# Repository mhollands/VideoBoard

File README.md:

# VideoBoard
Repo to hold files for the video board which was a prototype for the HP2VGA project

# Known Issues
Vsync and Hsync are swapped. C23 and C32 are unnecessary. Solution, use C23 and C32 footprints to swap the Vsync and Hsync inputs.

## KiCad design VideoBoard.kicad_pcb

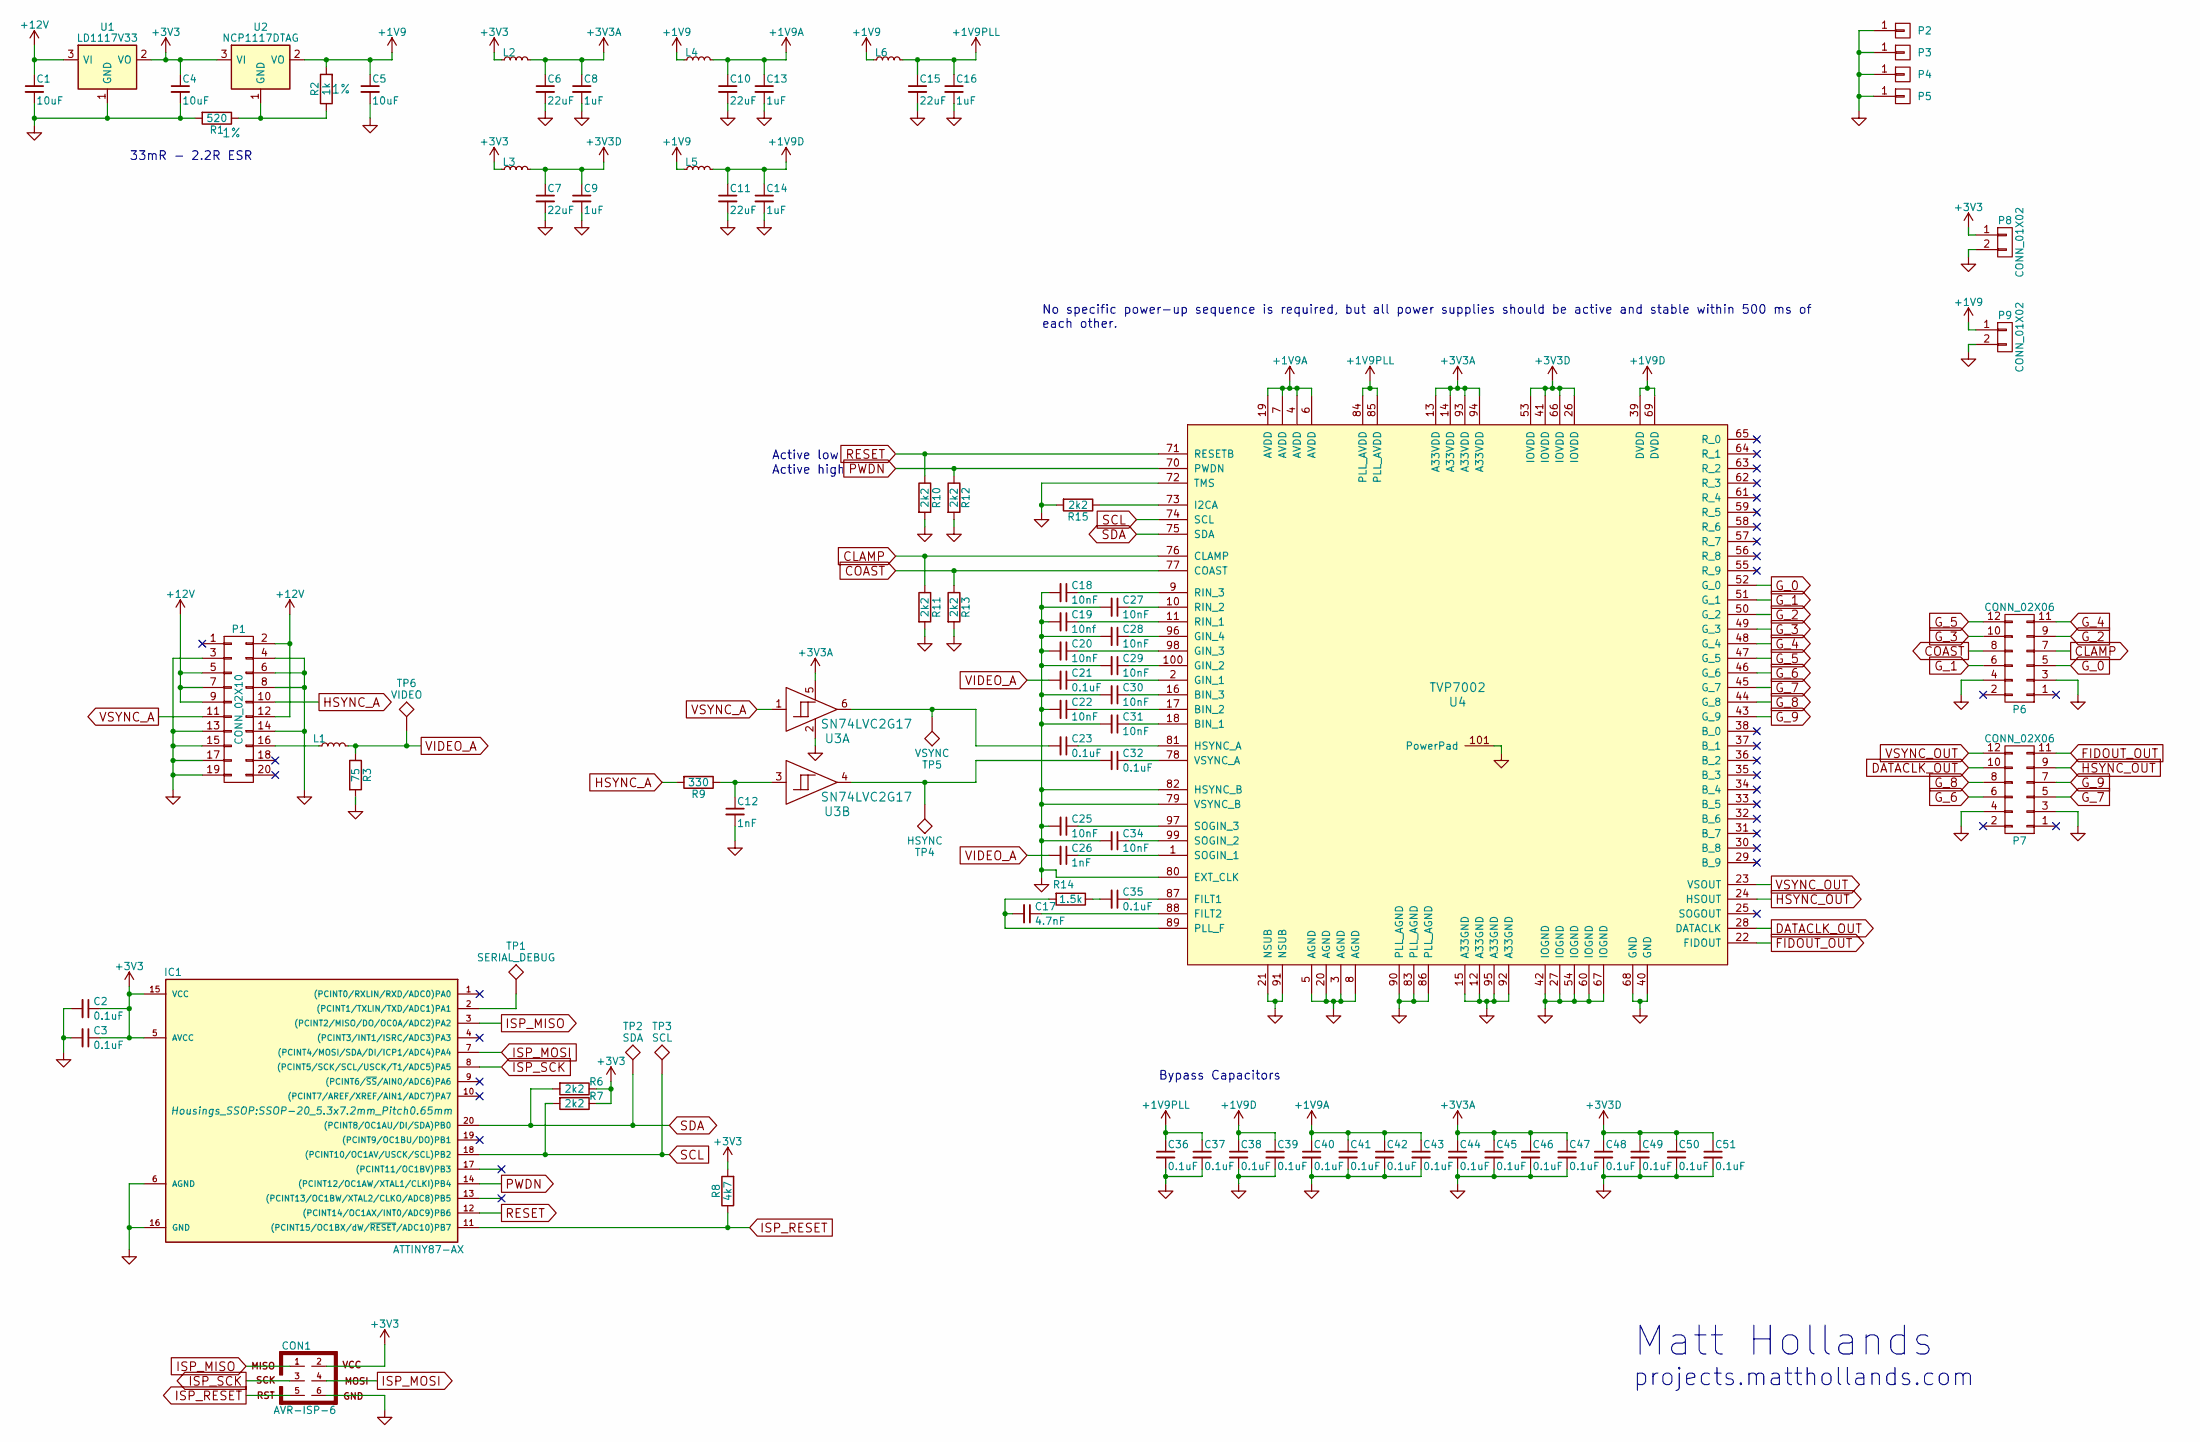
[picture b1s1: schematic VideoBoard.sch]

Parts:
C1, C4, C5: 10uF; CP_Radial_D5.0mm_P2.00mm; Digikey# 1189-2322-ND
C2, C3, C21, C23, C32, C35, C36, C37, C38, C39, C40, C41, C42, C43, C44, C45, C46, C47, C48, C49, C50, C51: 0.1uF; C_0603_HandSoldering
C6, C7, C10, C11, C15: 22uF; C_0603_HandSoldering
C8, C9, C13, C14, C16: 1uF; C_0603_HandSoldering
C12, C26: 1nF; C_0603_HandSoldering
C17: 4.7nF; C_0603_HandSoldering
C18, C20, C22, C25, C27, C28, C29, C30, C31, C34: 10nF; C_0603_HandSoldering
C19: 10nf; C_0603_HandSoldering
CON1: AVR-ISP-6; Pin_Header_Straight_2x03_Pitch2.54mm; Digikey# 609-5122-ND
IC1: ATTINY87-AX; SSOP-20_5.3x7.2mm_Pitch0.65mm
L1: L_Small; R_0603_HandSoldering
L2, L3, L4, L5, L6: L_Small; R_0603_HandSoldering; Digikey# MH1608-601YCT-ND
P1: CONN_02X10; Pin_Header_Straight_2x10_Pitch2.54mm
P2, P3, P4, P5: CONN_01X01; MountingHole_3.2mm_M3
P6, P7: CONN_02X06; Pin_Header_Angled_2x06_Pitch2.54mm
P8, P9: CONN_01X02; Pin_Header_Straight_1x02_Pitch2.54mm
R1: 520; R_0603_HandSoldering; Tolerance 1%
R2: 1k; R_0603_HandSoldering; Tolerance 1%
R3: 75; R_0603_HandSoldering
R6, R7, R10, R11, R12, R13, R15: 2k2; R_0603_HandSoldering
R8: 4k7; R_0603_HandSoldering
R9: 330; R_0603_HandSoldering
R14: 1.5k; R_0603_HandSoldering
TP1: SERIAL_DEBUG; Measurement_Point_Round-SMD-Pad_Small
TP2: SDA; Measurement_Point_Round-SMD-Pad_Small
TP3: SCL; Measurement_Point_Round-SMD-Pad_Small
TP4: HSYNC; Measurement_Point_Round-SMD-Pad_Small
TP5: VSYNC; Measurement_Point_Round-SMD-Pad_Small
TP6: VIDEO; Measurement_Point_Round-SMD-Pad_Small
U1: LD1117V33; TO-220_Vertical; Digikey# 497-1491-5-ND
U2: NCP1117DTAG; TO-252-2
U3: SN74LVC2G17; SOT-23-6_Handsoldering
U4: TVP7002; TQFP-100_14x14mm_Pitch0.5mm-PowerPad; Digikey# 296-22891-ND

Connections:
+1V9: C5.1, L4.1, L5.1, L6.1, P9.1, R2.2, U2.2 (VO)
+1V9A: C10.1, C13.1, C40.1, C41.1, C42.1, C43.1, L4.2, U4.4 (AVDD), U4.6 (AVDD), U4.7 (AVDD), U4.19 (AVDD)
+1V9D: C11.1, C14.1, C38.1, C39.1, L5.2, U4.39 (DVDD), U4.69 (DVDD)
+1V9PLL: C15.1, C16.1, C36.1, C37.1, L6.2, U4.84 (PLL_AVDD), U4.85 (PLL_AVDD)
+3V3: C2.1, C3.1, C4.1, CON1.2, IC1.5 (AVCC), IC1.15 (VCC), L2.1, L3.1, P8.1, R6.1, R7.1, R8.2, U1.2 (VO), U2.3 (VI)
+3V3A: C6.1, C8.1, C44.1, C45.1, C46.1, C47.1, L2.2, U3.5, U4.13 (A33VDD), U4.14 (A33VDD), U4.93 (A33VDD), U4.94 (A33VDD)
+3V3D: C7.1, C9.1, C48.1, C49.1, C50.1, C51.1, L3.2, U4.26 (IOVDD), U4.41 (IOVDD), U4.53 (IOVDD), U4.66 (IOVDD)
+12V: C1.1, P1.2, P1.5, P1.7, P1.9, P1.12, U1.3 (VI)
CLAMP: P6.7, R11.1, U4.76 (CLAMP)
COAST: P6.8, R13.1, U4.77 (COAST)
DATACLK_OUT: P7.10, U4.28 (DATACLK)
FIDOUT_OUT: P7.11, U4.22 (FIDOUT)
GND: C1.2, C2.2, C3.2, C4.2, C5.2, C6.2, C7.2, C8.2, C9.2, C10.2, C11.2, C12.2, C13.2, C14.2, C15.2, C16.2, C18.2, C19.2, C20.2, C22.2, C25.2, C27.2, C28.2, C29.2, C30.2, C31.2, C34.2, C36.2, C37.2, C38.2, C39.2, C40.2, C41.2, C42.2, C43.2, C44.2, C45.2, C46.2, C47.2, C48.2, C49.2, C50.2, C51.2, CON1.6, IC1.6 (AGND), IC1.16 (GND), P1.3, P1.4, P1.6, P1.8, P1.13, P1.14, P1.15, P1.17, P1.19, P2.1, P3.1, P4.1, P5.1, P6.3, P6.4, P7.3, P7.4, P8.2, P9.2, R1.2, R3.2, R10.2, R11.2, R12.2, R13.2, R15.2, U1.1 (GND), U3.2, U4.3 (AGND), U4.5 (AGND), U4.8 (AGND), U4.12 (A33GND), U4.15 (A33GND), U4.20 (AGND), U4.21 (NSUB), U4.27 (IOGND), U4.40 (GND), U4.42 (IOGND), U4.54 (IOGND), U4.60 (IOGND), U4.67 (IOGND), U4.68 (GND), U4.72 (TMS), U4.79 (VSYNC_B), U4.80 (EXT_CLK), U4.82 (HSYNC_B), U4.83 (PLL_AGND), U4.86 (PLL_AGND), U4.90 (PLL_AGND), U4.91 (NSUB), U4.92 (A33GND), U4.95 (A33GND), U4.101 (PowerPad)
G_0: P6.5, U4.52 (G_0)
G_1: P6.6, U4.51 (G_1)
G_2: P6.9, U4.50 (G_2)
G_3: P6.10, U4.49 (G_3)
G_4: P6.11, U4.48 (G_4)
G_5: P6.12, U4.47 (G_5)
G_6: P7.6, U4.46 (G_6)
G_7: P7.5, U4.45 (G_7)
G_8: P7.8, U4.44 (G_8)
G_9: P7.7, U4.43 (G_9)
HSYNC_A: P1.10, R9.2
HSYNC_OUT: P7.9, U4.24 (HSOUT)
ISP_MISO: CON1.1, IC1.3 ((PCINT2/MISO/DO/OC0A/ADC2)PA2)
ISP_MOSI: CON1.4, IC1.7 ((PCINT4/MOSI/SDA/DI/ICP1/ADC4)PA4)
ISP_RESET: CON1.5, IC1.11 ((PCINT15/OC1BX/dW/~RESET~/ADC10)PB7), R8.1
ISP_SCK: CON1.3, IC1.8 ((PCINT5/SCK/SCL/USCK/T1/ADC5)PA5)
unnamed: C12.1, R9.1, U3.3
unnamed: C17.1, U4.88 (FILT2)
unnamed: C17.2, R14.2, U4.89 (PLL_F)
unnamed: C18.1, U4.9 (RIN_3)
unnamed: C19.1, U4.11 (RIN_1)
unnamed: C20.1, U4.98 (GIN_3)
unnamed: C21.1, U4.2 (GIN_1)
unnamed: C22.1, U4.17 (BIN_2)
unnamed: C23.1, U4.81 (HSYNC_A)
unnamed: C23.2, TP5.1, U3.6
unnamed: C25.1, U4.97 (SOGIN_3)
unnamed: C26.1, U4.1 (SOGIN_1)
unnamed: C27.1, U4.10 (RIN_2)
unnamed: C28.1, U4.96 (GIN_4)
unnamed: C29.1, U4.100 (GIN_2)
unnamed: C30.1, U4.16 (BIN_3)
unnamed: C31.1, U4.18 (BIN_1)
unnamed: C32.1, U4.78 (VSYNC_A)
unnamed: C32.2, TP4.1, U3.4
unnamed: C34.1, U4.99 (SOGIN_2)
unnamed: C35.1, U4.87 (FILT1)
unnamed: C35.2, R14.1
unnamed: IC1.2 ((PCINT1/TXLIN/TXD/ADC1)PA1), TP1.1
unnamed: L1.1, P1.16
unnamed: R1.1, R2.1, U2.1 (GND)
unnamed: R15.1, U4.73 (I2CA)
PWDN: IC1.14 ((PCINT12/OC1AW/XTAL1/CLKI)PB4), R12.1, U4.70 (PWDN)
RESET: IC1.12 ((PCINT14/OC1AX/INT0/ADC9)PB6), R10.1, U4.71 (RESETB)
SCL: IC1.18 ((PCINT10/OC1AV/USCK/SCL)PB2), R7.2, TP3.1, U4.74 (SCL)
SDA: IC1.20 ((PCINT8/OC1AU/DI/SDA)PB0), R6.2, TP2.1, U4.75 (SDA)
VIDEO_A: C21.2, C26.2, L1.2, R3.1, TP6.1
VSYNC_A: P1.11, U3.1
VSYNC_OUT: P7.12, U4.23 (VSOUT)

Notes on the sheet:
No specific power-up sequence is required, but all power supplies should be active and stable within 500 ms of each other.
Bypass Capacitors
Active low
Active high
33mR - 2.2R ESR
Matt Hollands
projects.matthollands.com

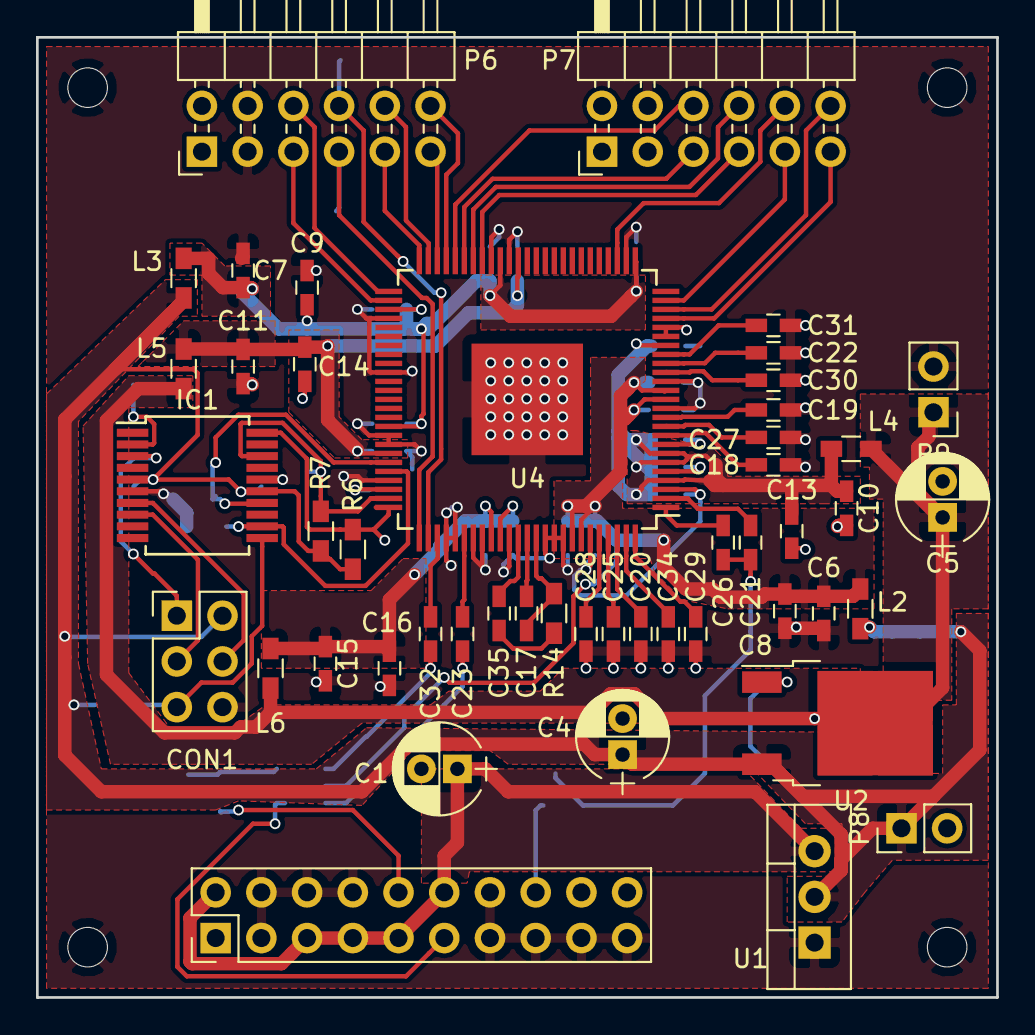
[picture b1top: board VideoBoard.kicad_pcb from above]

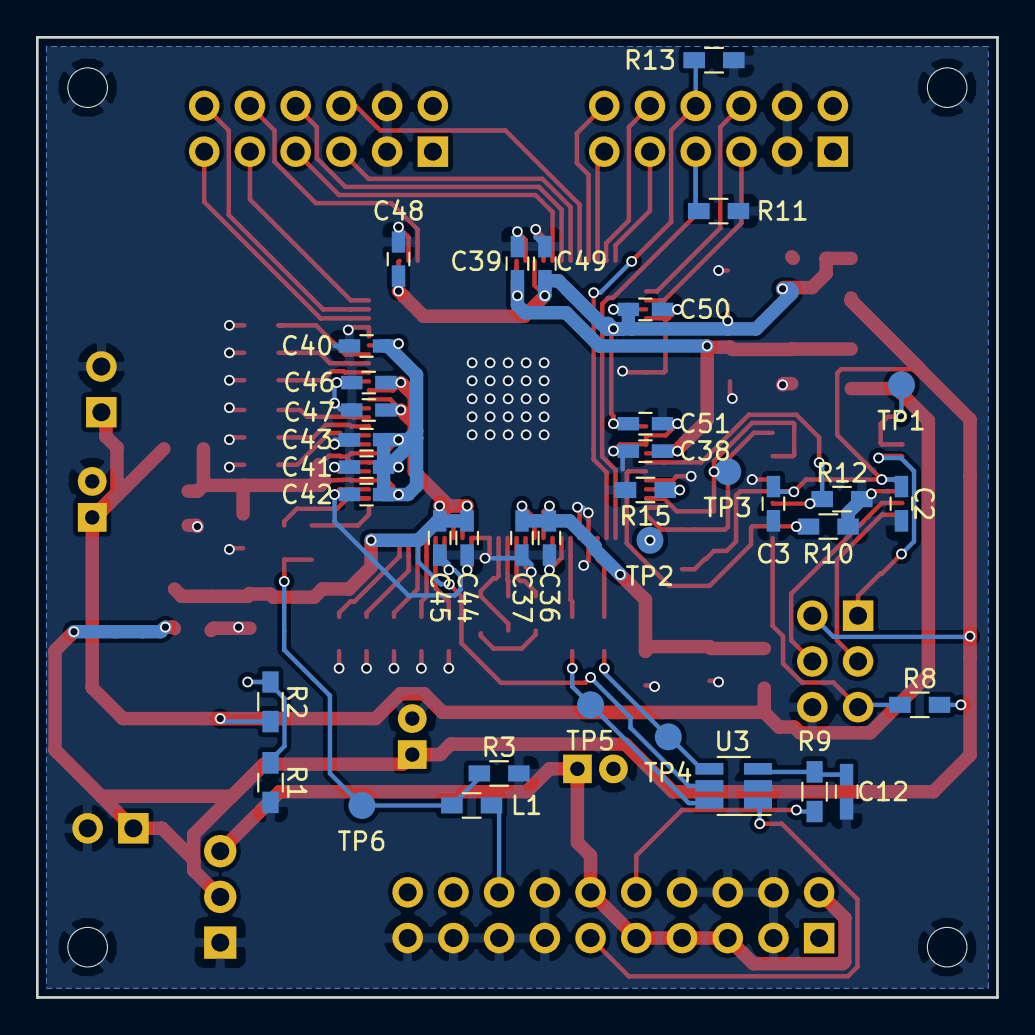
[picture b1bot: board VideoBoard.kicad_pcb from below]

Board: 2 copper layers, 53.3 x 53.3 mm, 89 parts (37 on the bottom side), 62 nets.

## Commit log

2020-05-30 Add everything
